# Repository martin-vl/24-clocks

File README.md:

# 24-clocks
24 clocks represents one digital clock

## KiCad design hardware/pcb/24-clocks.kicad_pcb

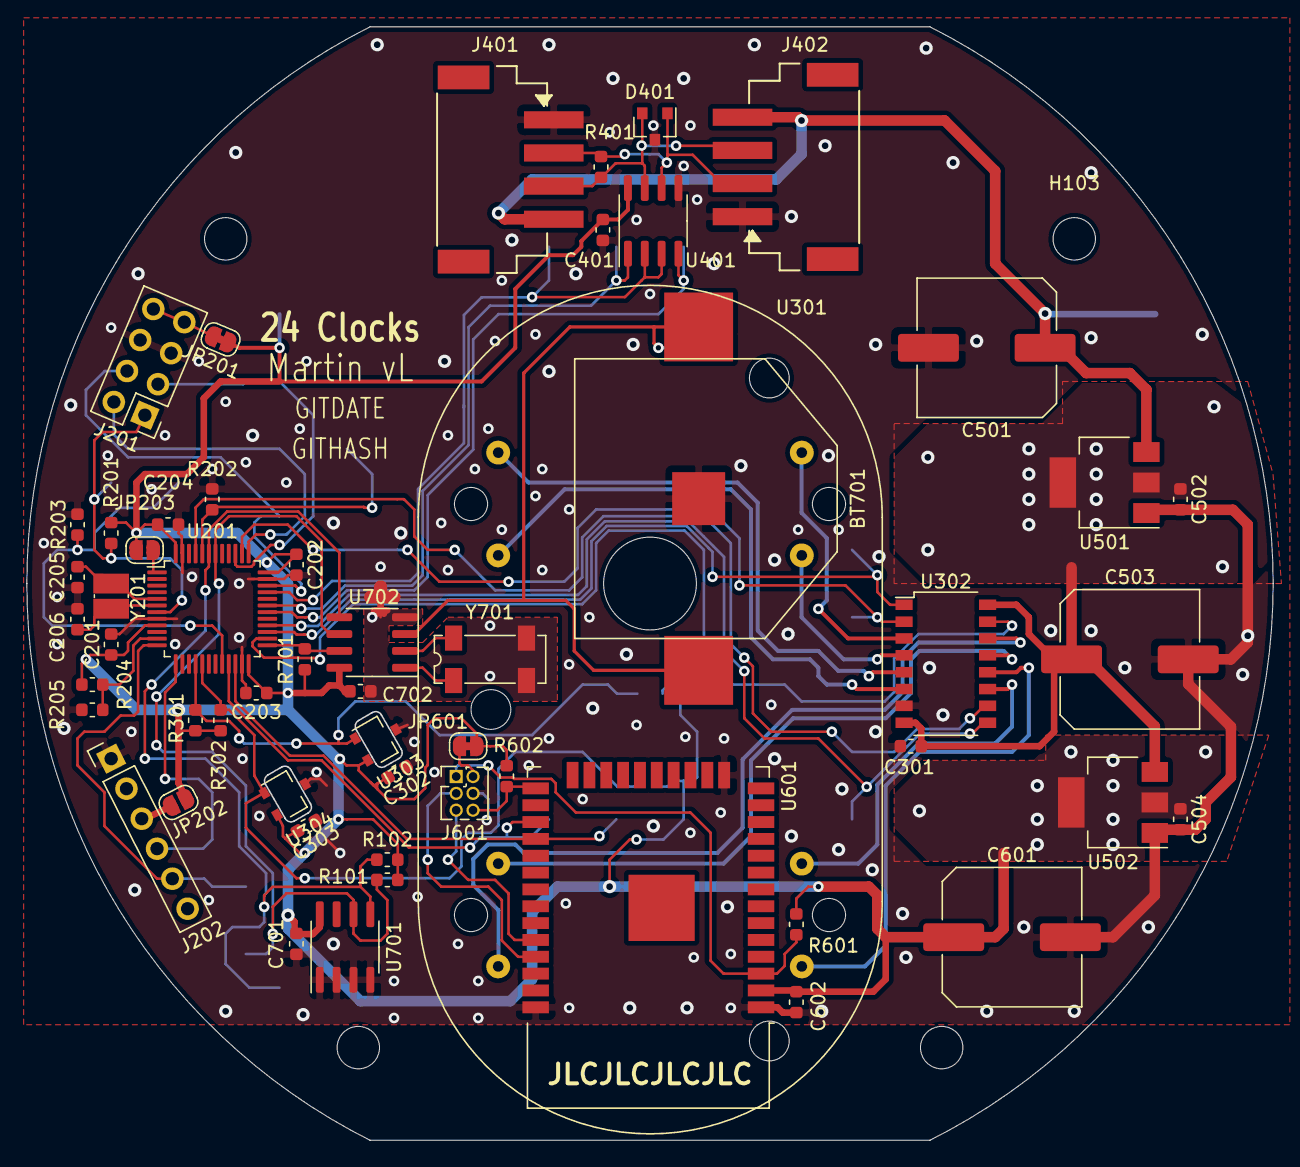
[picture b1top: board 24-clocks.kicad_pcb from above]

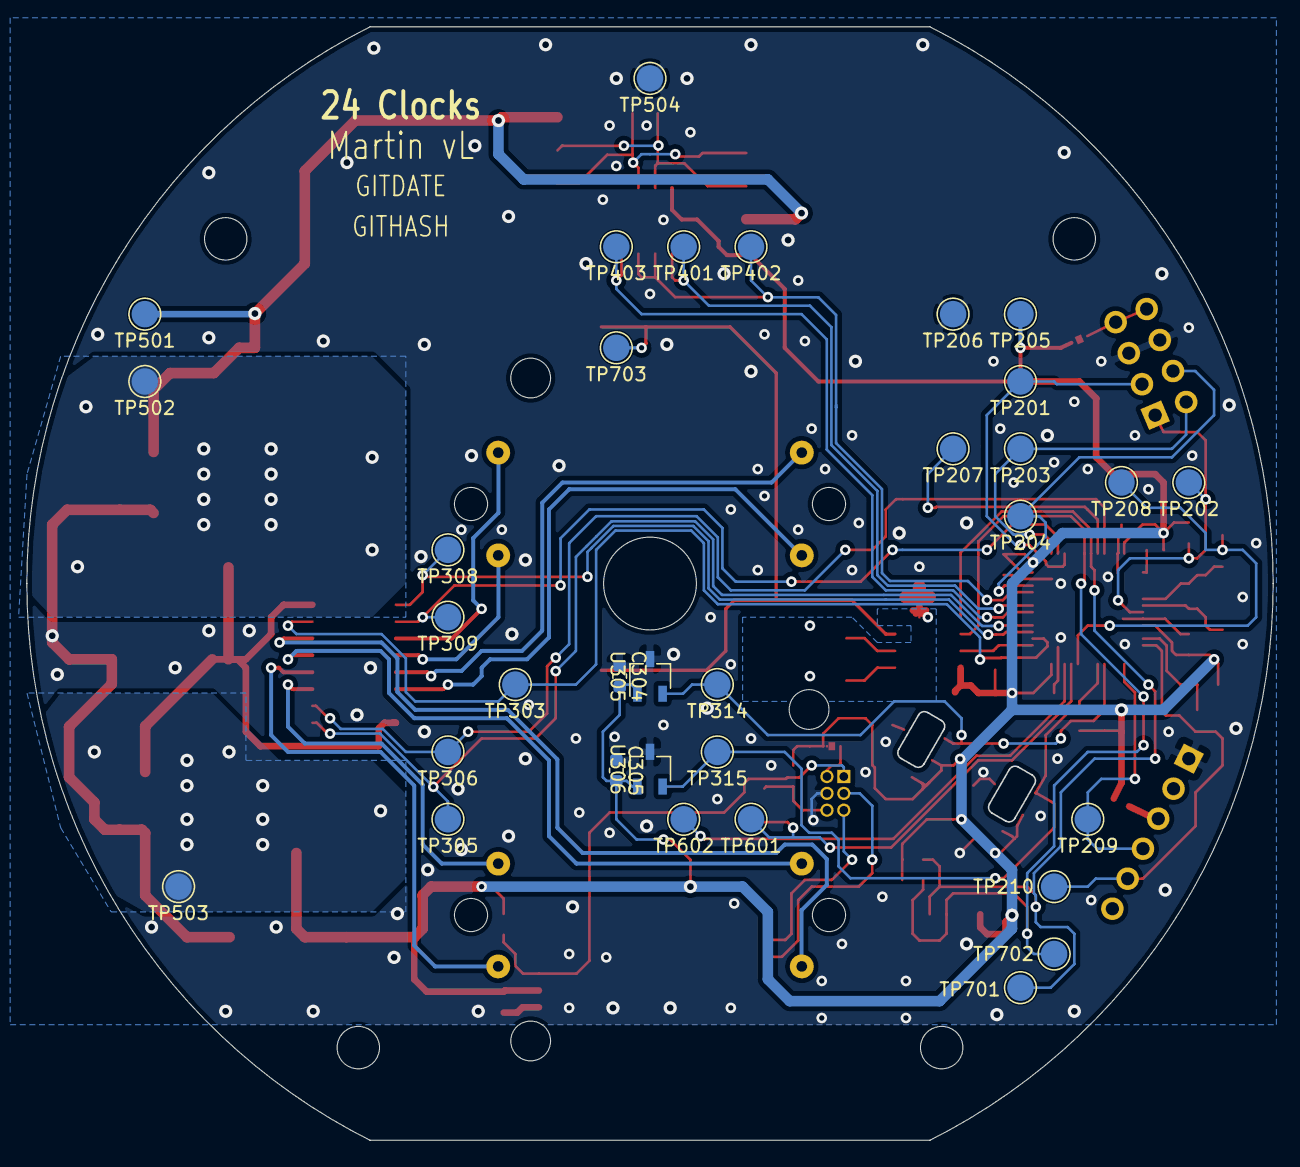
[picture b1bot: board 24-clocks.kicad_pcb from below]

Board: 2 copper layers, 93.9 x 83.9 mm, 93 parts (33 on the bottom side), 52 nets.

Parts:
BT701: CR2032; BATT_WE_79523141
C201, C202, C203, C204, C301, C302, C303, C304, C305, C401, C502, C504, C602, C701, C702: 100nF; C_0603_1608Metric
C205, C206: 20pF; C_0603_1608Metric
C501, C503, C601: 22uF; C_Elec_10x10.2
D401: PESD1CAN; SOT-23
H101, H102, H103, H104: MountingHole; MountingHole_3.2mm_M3
J201: ST-LINK; PinHeader_2x04_P2.54mm_Vertical
J202: Debug UART; PinHeader_1x06_P2.54mm_Vertical
J401, J402: S4B_XH_SM4_TB; JST_S4B_XH_SM4_TB
J601: Conn_02x03_Odd_Even; PinHeader_2x03_P1.27mm_Vertical
JP201, JP601: Jumper_NC_Small; SolderJumper-2_P1.3mm_Bridged_RoundedPad1.0x1.5mm
JP202, JP203: Jumper_NO_Small; SolderJumper-2_P1.3mm_Open_RoundedPad1.0x1.5mm
NT701: Net-Tie_2; NetTie-2_SMD_Pad0.5mm
R101, R102: 5k; R_0603_1608Metric
R201: 4k7; R_0603_1608Metric
R202, R203, R204, R205, R301, R302, R601, R602, R701: 10k; R_0603_1608Metric
R401: 120E; R_0603_1608Metric
TP201: SWO; TestPoint_Pad_D2.0mm
TP202: uC-Rst; TestPoint_Pad_D2.0mm
TP203: SWDCLK; TestPoint_Pad_D2.0mm
TP204: SWDIO; TestPoint_Pad_D2.0mm
TP205: 3V3; TestPoint_Pad_D2.0mm
TP206, TP504: GND; TestPoint_Pad_D2.0mm
TP207: BOOT0; TestPoint_Pad_D2.0mm
TP208: BOOT1; TestPoint_Pad_D2.0mm
TP209: uC-Debug-Rx; TestPoint_Pad_D2.0mm
TP210: uC-Debug-Tx; TestPoint_Pad_D2.0mm
TP303: M-Rst; TestPoint_Pad_D2.0mm
TP305: M-A-CW; TestPoint_Pad_D2.0mm
TP306: M-A-Step; TestPoint_Pad_D2.0mm
TP308: M-B-CW; TestPoint_Pad_D2.0mm
TP309: M-B-Step; TestPoint_Pad_D2.0mm
TP314: HAL-A; TestPoint_Pad_D2.0mm
TP315: HAL-B; TestPoint_Pad_D2.0mm
TP401: uC-RS485-Rx; TestPoint_Pad_D2.0mm
TP402: uC-RS485-DE; TestPoint_Pad_D2.0mm
TP403: uC-RS485-Tx; TestPoint_Pad_D2.0mm
TP501: +9V; TestPoint_Pad_D2.0mm
TP502: +5V; TestPoint_Pad_D2.0mm
TP503: +3V3; TestPoint_Pad_D2.0mm
TP601: uC-WiFi-Tx; TestPoint_Pad_D2.0mm
TP602: uC-WiFi-Rx; TestPoint_Pad_D2.0mm
TP701: I2C-SDA; TestPoint_Pad_D2.0mm
TP702: I2C-SCL; TestPoint_Pad_D2.0mm
TP703: RC2032; TestPoint_Pad_D2.0mm
U201: STM32F103C8Tx; LQFP-48_7x7mm_P0.5mm
U301: VID28-05; BK30D-R5
U302: VID66-08; SOP-16_4.4x10.4mm_P1.27mm
U303, U304: AH3572; SOT-23-UD
U305, U306: AH3572; TSOT-23
U401: MAX3485; SOIC-8_3.9x4.9mm_P1.27mm
U501: AMS1117-5.0; SOT-223-3_TabPin2
U502: AMS1117-3.3; SOT-223-3_TabPin2
U601: ESP32-WROOM-32D; ESP32-WROOM-32
U701: 24LC512; SOIC-8_3.9x4.9mm_P1.27mm
U702: DS1307+; SOIC-8_3.9x4.9mm_P1.27mm
Y201: NX3225GD 8MHz; Crystal_SMD_3225-2Pin_3.2x2.5mm
Y701: 32.768kHz; Crystal_SMD_SeikoEpson_MC306-4Pin_8.0x3.2mm

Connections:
+3V3: C201.1, C202.1, C203.1, C204.1, C302.2, C303.2, C304.2, C305.2, C401.1, C504.1, C601.1, C602.1, C701.1, C702.1, JP201.1, JP202.1, JP203.1, JP601.2, R101.1, R102.1, R201.1, R204.1, R301.1, R302.1, R601.1, R602.1, R701.1, TP205.1, TP503.1, U201.9, U201.24, U201.36, U201.48, U303.1, U304.1, U305.1, U306.1, U401.8, U502.2, U601.2, U701.8, U702.8
+5V: C301.2, C502.1, C503.1, TP502.1, U302.8, U302.16, U501.2, U502.3
+7.5V: C501.1, J401.4, J402.4, TP501.1, U501.3
/Com Bus/RS485-A: D401.1, J401.2, J402.2, R401.2, U401.6
/Com Bus/RS485-B: D401.2, J401.3, J402.3, R401.1, U401.7
/Com Bus/uC-RS485-DE: TP402.1, U201.33, U401.2, U401.3
/Com Bus/uC-RS485-Rx: TP401.1, U201.31, U401.1
/Com Bus/uC-RS485-Tx: TP403.1, U201.30, U401.4
/I2C-SCL: R101.2, TP702.1, U201.42, U701.6, U702.6
/I2C-SDA: R102.2, TP701.1, U201.43, U701.5, U702.5
/Mechanics/HAL-A: R301.2, TP314.1, U201.16, U303.2, U305.2
/Mechanics/HAL-B: R302.2, TP315.1, U201.17, U304.2, U306.2
/Mechanics/M-A-CW: TP305.1, U201.28, U302.9
/Mechanics/M-A-Step: TP306.1, U201.45, U302.10
/Mechanics/M-B-CW: TP308.1, U201.27, U302.1
/Mechanics/M-B-Step: TP309.1, U201.38, U302.2
/Mechanics/M-Rst: TP303.1, U201.26, U302.15
/Mechanics/MA1: U301.1, U302.3
/Mechanics/MA2: U301.2, U302.4
/Mechanics/MA3: U301.3, U302.6
/Mechanics/MA4: U301.4, U302.5
/Mechanics/MB1: U301.5, U302.11
/Mechanics/MB2: U301.6, U302.12
/Mechanics/MB3: U301.7, U302.14
/Mechanics/MB4: U301.8, U302.13
/RTC and Memory/GND-CLK: C702.2, NT701.1, U702.4, Y701.2, Y701.3
/RTC and Memory/RTC-CLK: R701.2, U201.25, U702.7
/RTC and Memory/Vbat: BT701.1, BT701.3, TP703.1, U702.3
/WiFi/ESP-EN: J601.1, R601.2, U601.3
/WiFi/ESP-IO0: J601.6, R602.2, U601.25
/WiFi/ESP-RxD0: J601.5, U601.34
/WiFi/ESP-TxD0: J601.3, U601.35
/WiFi/uC-WiFi-Rx: TP602.1, U201.22, U601.28
/WiFi/uC-WiFi-Tx: TP601.1, U201.21, U601.27
/uC/BOOT0: R202.1, TP207.1, U201.44
/uC/BOOT1: R203.1, TP208.1, U201.20
/uC/HW-Version: R204.2, R205.1, U201.11
/uC/SWDCLK: J201.2, TP203.1, U201.37
/uC/SWDIO: J201.4, TP204.1, U201.34
/uC/SWO: J201.3, TP201.1, U201.39
/uC/uC-Debug-Rx: J202.4, TP209.1, U201.13
/uC/uC-Debug-Tx: J202.5, TP210.1, U201.12
/uC/uC-RST: J201.1, R201.2, TP202.1, U201.7
GND: BT701.2, C201.2, C202.2, C203.2, C204.2, C205.2, C206.2, C301.1, C302.1, C303.1, C304.1, C305.1, C401.2, C501.2, C502.2, C503.2, C504.2, C601.2, C602.2, C701.2, D401.3, J201.5, J201.6, J202.1, J401.1, J402.1, J601.4, NT701.2, R202.2, R203.2, R205.2, TP206.1, TP504.1, U201.8, U201.23, U201.35, U201.47, U302.7, U303.3, U304.3, U305.3, U306.3, U401.5, U501.1, U502.1, U601.1, U601.15, U601.38, U701.1, U701.2, U701.3, U701.4
unnamed: C205.1, U201.5, Y201.1
unnamed: C206.1, U201.6, Y201.2
unnamed: J201.7, J201.8, JP201.2
unnamed: J202.3, JP202.2
unnamed: J601.2, JP601.1
unnamed: JP203.2, U201.1
unnamed: U702.1, Y701.1
unnamed: U702.2, Y701.4

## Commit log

2020-11-29 Initial schematic
2020-12-03 Create Makefile
2020-12-03 Rename .github/workflow-pcb.yml to .github/workflow/pcb.yml
2020-12-03 Update Makefile
2020-12-03 moved makefile
2020-12-03 change output dir
2020-12-05 updated makefile for pcb
2020-12-05 Updated run script
2020-12-05 Minor
2020-12-06 Change schematic to hierarchical design
2020-12-06 Changed uC
2020-12-11 Created variants
2020-12-11 Added debug connector
2020-12-11 Draft schematic (#1)
    * Change schematic to hierarchical design
    * Changed uC
    * Created variants
    * Added debug connector
2020-12-23 Updated processor pins and added testpoints
2020-12-24 Small changes
2020-12-25 Updated footprints
2020-12-25 changed crystals
2020-12-26 Created footprints and archived project
2020-12-27 Added motor footprint, made init pcb
2020-12-27 Footprints (#2)
    * Changed uC
    * Updated processor pins and added testpoints
    * Small changes
    * Updated footprints
    * changed crystals
    * Created footprints and archived project
2020-12-28 Created PCB outline and first placement
2020-12-31 Changed connectors
2021-01-02 Included all 3D files
2021-01-10 Mixed changes
2021-01-10 Changed supply to 7V
2021-01-18 Archived PCB project
2021-01-18 First placement
2021-01-19 Routed supplies
2021-01-22 Added routing
2021-01-31 Routed more nets
2021-02-07 Finished routing
2021-02-07 Archived project
2021-02-07 Replace hash and date
2021-02-12 Auto update commit date and hash
2021-02-12 Update output
2021-02-12 changed outputs
2021-02-12 Added layer to output
2021-02-12 Update hash and date also in sch
2021-02-12 Added caps to hall sensors
2021-02-12 Cleanup files
2021-02-12 Finished PCB (#3)
    * Created PCB outline and first placement
    * Changed connectors
    * Minor
    * Included all 3D files
    * Mixed changes
    * Changed supply to 7V
2021-03-07 Init slave software
2022-08-20 Steppers running + pass through master
